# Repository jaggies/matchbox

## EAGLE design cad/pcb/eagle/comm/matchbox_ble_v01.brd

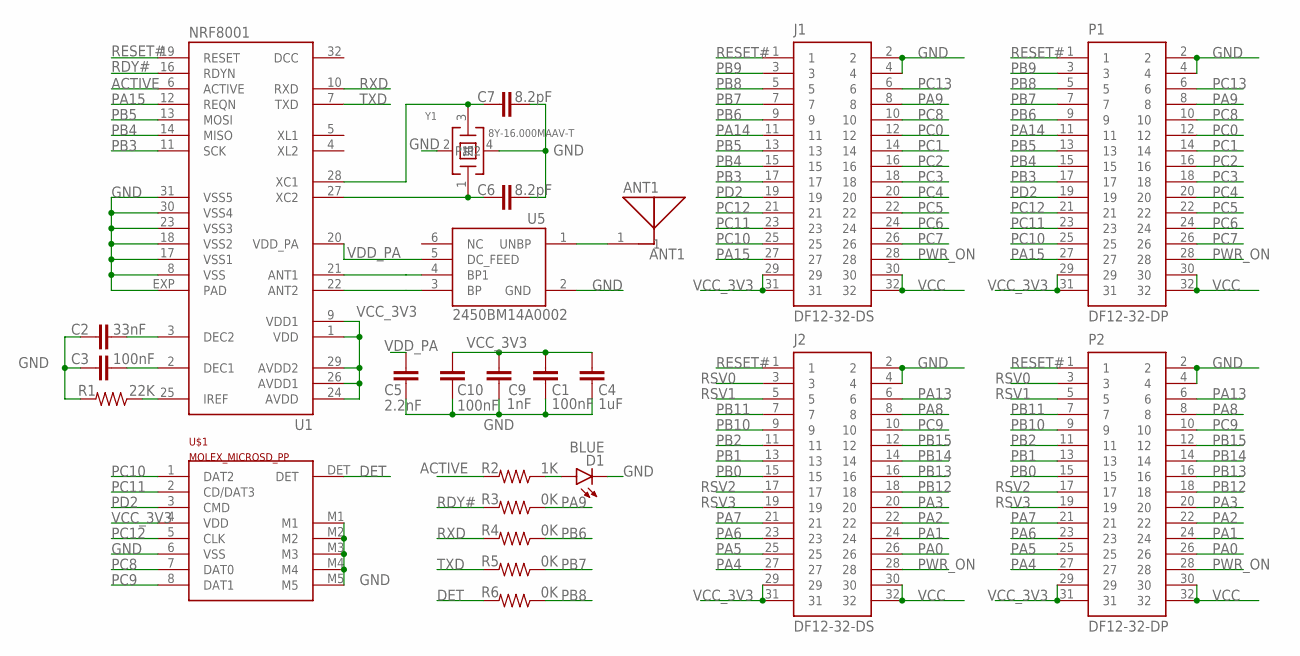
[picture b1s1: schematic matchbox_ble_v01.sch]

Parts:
ANT1: ANT1; 2450AT18A100; PARTNO AS-ITM-00132
C1, C3, C10: 100nF; 0402-CAP; MPN 1C20Z5U104M050B
C2: 33nF; 0402-CAP
C4: 1uF; 0805
C5: 2.2nF; 0402-CAP
C6, C7: 8.2pF; 0402-CAP
C9: 1nF; 0402-CAP
D1: BLUE; LED-0603
J1, J2: DF12-32-DS
P1, P2: DF12-32-DP
R1: 22K; 0402-RES
R2: 1K; 0805
R3, R4, R5, R6: 0K; 0805
U1: NRF8001; ATMEL_QFN32
U5: 2450BM14A0002
U$1: MOLEX_MICROSD_PP
Y1: 8Y-16.000MAAV-T; ABM11; PARTNO AS-ITM-00228

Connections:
ACTIVE: R2.2, U1.6 (ACTIVE)
ANT1: U1.21 (ANT1), U5.4 (BP1)
ANT2: U1.22 (ANT2), U5.3 (BP)
DET: R6.2, U$1.DET
GND: C1.2, C2.2, C3.2, C4.2, C5.2, C6.2, C7.2, C9.2, C10.2, D1.C, J1.2, J1.4, J2.2, J2.4, P1.2, P1.4, P2.2, P2.4, R1.2, U1.8 (VSS), U1.17 (VSS1), U1.18 (VSS2), U1.23 (VSS3), U1.30 (VSS4), U1.31 (VSS5), U1.EXP (PAD), U5.2 (GND), U$1.6 (VSS), U$1.M1, U$1.M2, U$1.M3, U$1.M4, U$1.M5, Y1.2, Y1.4 (P1)
unnamed: R1.1, U1.25 (IREF)
unnamed: C6.1, U1.27 (XC2), Y1.1
unnamed: C3.1, U1.2 (DEC1)
unnamed: C2.1, U1.3 (DEC2)
unnamed: ANT1.1, U5.1 (UNBP)
unnamed: C7.1, U1.28 (XC1), Y1.3 (2)
unnamed: D1.A, R2.1
PA0: J2.26, P2.26
PA1: J2.24, P2.24
PA2: J2.22, P2.22
PA3: J2.20, P2.20
PA4: J2.27, P2.27
PA5: J2.25, P2.25
PA6: J2.23, P2.23
PA7: J2.21, P2.21
PA8: J2.8, P2.8
PA9: J1.8, P1.8, R3.1
PA13: J2.6, P2.6
PA14: J1.11, P1.11
PA15: J1.27, P1.27, U1.12 (REQN)
PB0: J2.15, P2.15
PB1: J2.13, P2.13
PB2: J2.11, P2.11
PB3: J1.17, P1.17, U1.11 (SCK)
PB4: J1.15, P1.15, U1.14 (MISO)
PB5: J1.13, P1.13, U1.13 (MOSI)
PB6: J1.9, P1.9, R4.1
PB7: J1.7, P1.7, R5.1
PB8: J1.5, P1.5, R6.1
PB9: J1.3, P1.3
PB10: J2.9, P2.9
PB11: J2.7, P2.7
PB12: J2.18, P2.18
PB13: J2.16, P2.16
PB14: J2.14, P2.14
PB15: J2.12, P2.12
PC0: J1.12, P1.12
PC1: J1.14, P1.14
PC2: J1.16, P1.16
PC3: J1.18, P1.18
PC4: J1.20, P1.20
PC5: J1.22, P1.22
PC6: J1.24, P1.24
PC7: J1.26, P1.26
PC8: J1.10, P1.10, U$1.7 (DAT0)
PC9: J2.10, P2.10, U$1.8 (DAT1)
PC10: J1.25, P1.25, U$1.1 (DAT2)
PC11: J1.23, P1.23, U$1.2 (CD/DAT3)
PC12: J1.21, P1.21, U$1.5 (CLK)
PC13: J1.6, P1.6
PD2: J1.19, P1.19, U$1.3 (CMD)
PWR_ON: J1.28, J2.28, P1.28, P2.28
RDY#: R3.2, U1.16 (RDYN)
RESET#: J1.1, J2.1, P1.1, P2.1, U1.19 (RESET)
RSV0: J2.3, P2.3
RSV1: J2.5, P2.5
RSV2: J2.17, P2.17
RSV3: J2.19, P2.19
RXD: R4.2, U1.10 (RXD)
TXD: R5.2, U1.7 (TXD)
VCC: J1.30, J1.32, J2.30, J2.32, P1.30, P1.32, P2.30, P2.32
VCC_3V3: C1.1, C4.1, C9.1, C10.1, J1.29, J1.31, J2.29, J2.31, P1.29, P1.31, P2.29, P2.31, U1.1 (VDD), U1.9 (VDD1), U1.24 (AVDD), U1.26 (AVDD1), U1.29 (AVDD2), U$1.4 (VDD)
VDD_PA: C5.1, U1.20 (VDD_PA), U5.5 (DC_FEED)

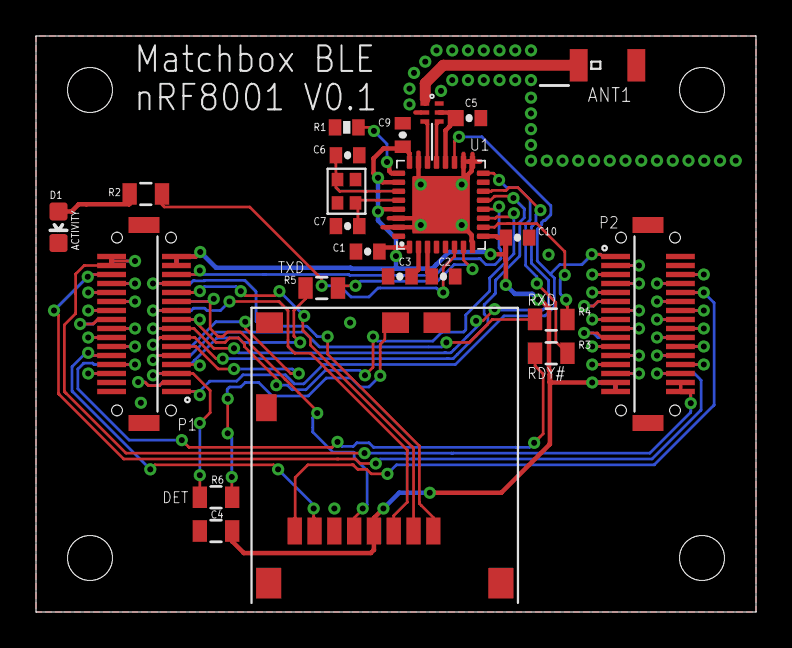
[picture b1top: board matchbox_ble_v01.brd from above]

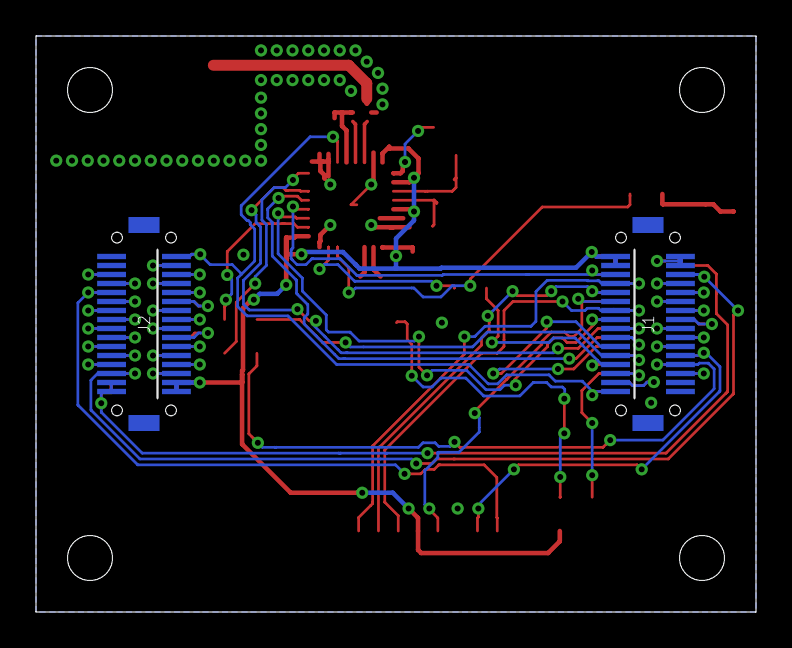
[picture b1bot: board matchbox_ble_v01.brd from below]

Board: 2 copper layers, 40.0 x 32.0 mm, 25 parts (2 on the bottom side), 68 nets.

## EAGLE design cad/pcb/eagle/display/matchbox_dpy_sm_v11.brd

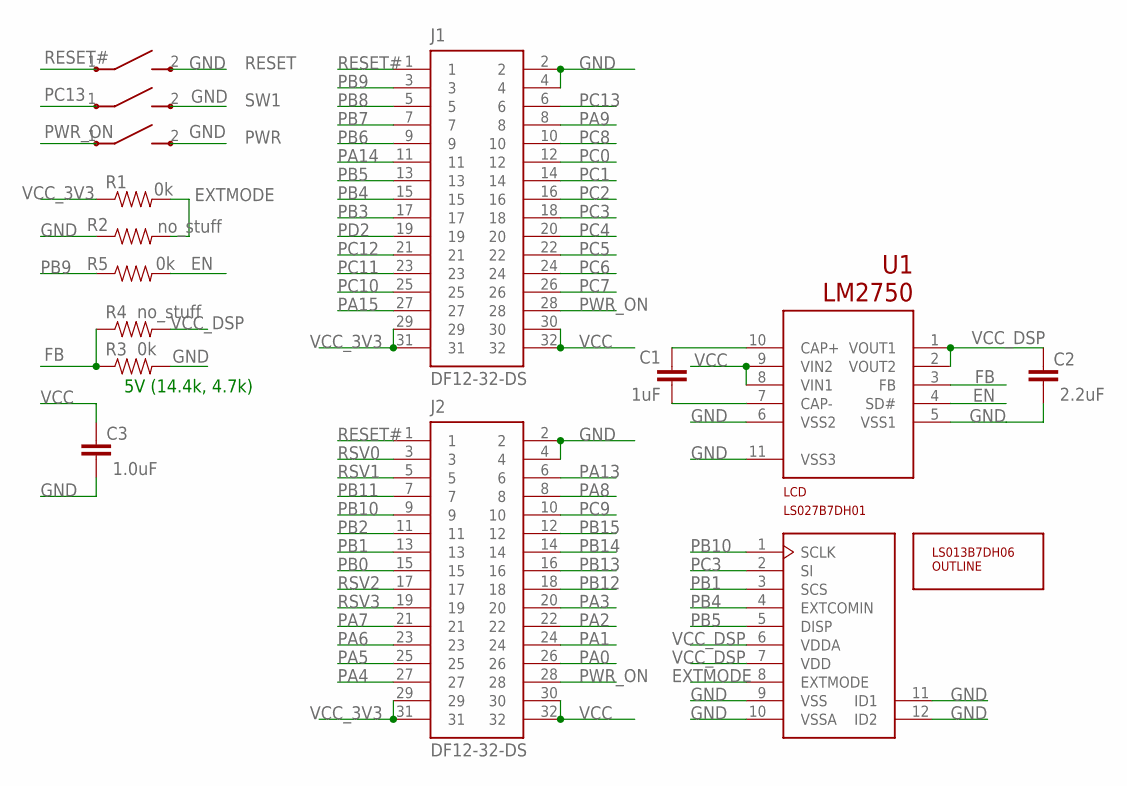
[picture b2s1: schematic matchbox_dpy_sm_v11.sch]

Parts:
C1: 1uF; 0805; MPN 106K050CS4
C2: 2.2uF; 0805; MPN 106K050CS4
C3: 1.0uF; 0805; MPN 106K050CS4
J1, J2: DF12-32-DS
LCD: LS027B7DH01; MOLEX-51441-1093
PWR: B3U-3100PM-B
R1, R3, R5: 0k; 0805
R2, R4: no_stuff; 0805
RESET: B3U-3100PM-B
SW1: B3U-3100PM-B
U1: LM2750
U$1: LS013B7DH06-OUTLINE; LS013B7DH06

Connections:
EN: R5.2, U1.4 (SD#)
EXTMODE: LCD.8 (EXTMODE), R1.2, R2.2
FB: R3.1, R4.1, U1.3 (FB)
GND: C2.2, C3.2, J1.2, J1.4, J2.2, J2.4, LCD.9 (VSS), LCD.10 (VSSA), LCD.11 (ID1), LCD.12 (ID2), PWR.2, PWR.GND, R2.1, R3.2, RESET.2, RESET.GND, SW1.2, SW1.GND, U1.5 (VSS1), U1.6 (VSS2), U1.11 (VSS3)
unnamed: C1.1, U1.10 (CAP+)
unnamed: C1.2, U1.7 (CAP-)
PA0: J2.26
PA1: J2.24
PA2: J2.22
PA3: J2.20
PA4: J2.27
PA5: J2.25
PA6: J2.23
PA7: J2.21
PA8: J2.8
PA9: J1.8
PA13: J2.6
PA14: J1.11
PA15: J1.27
PB0: J2.15
PB1: J2.13, LCD.3 (SCS)
PB2: J2.11
PB3: J1.17
PB4: J1.15, LCD.4 (EXTCOMIN)
PB5: J1.13, LCD.5 (DISP)
PB6: J1.9
PB7: J1.7
PB8: J1.5
PB9: J1.3, R5.1
PB10: J2.9, LCD.1 (SCLK)
PB11: J2.7
PB12: J2.18
PB13: J2.16
PB14: J2.14
PB15: J2.12
PC0: J1.12
PC1: J1.14
PC2: J1.16
PC3: J1.18, LCD.2 (SI)
PC4: J1.20
PC5: J1.22
PC6: J1.24
PC7: J1.26
PC8: J1.10
PC9: J2.10
PC10: J1.25
PC11: J1.23
PC12: J1.21
PC13: J1.6, SW1.1
PD2: J1.19
PWR_ON: J1.28, J2.28, PWR.1
RESET#: J1.1, J2.1, RESET.1
RSV0: J2.3
RSV1: J2.5
RSV2: J2.17
RSV3: J2.19
VCC: C3.1, J1.30, J1.32, J2.30, J2.32, U1.8 (VIN1), U1.9 (VIN2)
VCC_3V3: J1.29, J1.31, J2.29, J2.31, R1.1
VCC_DSP: C2.1, LCD.6 (VDDA), LCD.7 (VDD), R4.2, U1.1 (VOUT1), U1.2 (VOUT2)

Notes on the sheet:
5V (14.4k, 4.7k)

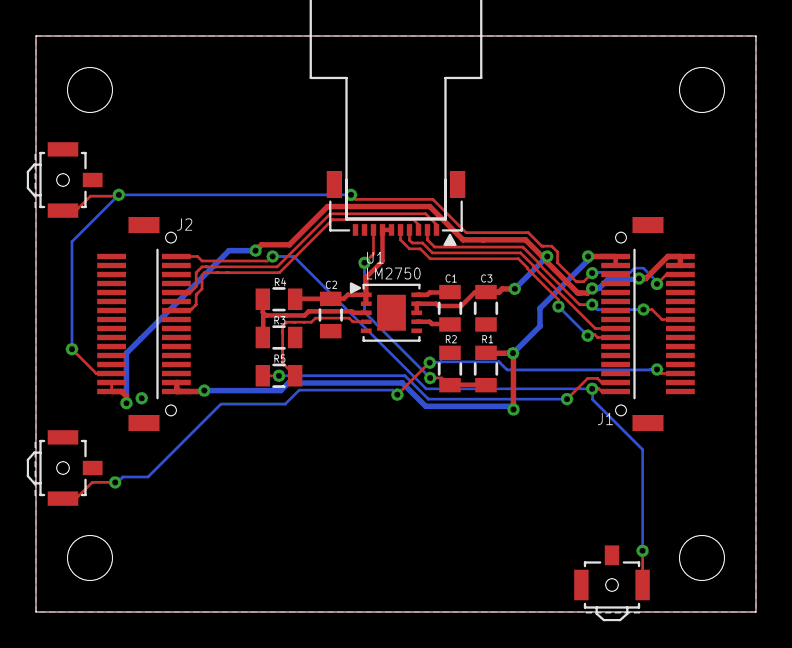
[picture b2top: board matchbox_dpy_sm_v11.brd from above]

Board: 2 copper layers, 40.0 x 32.0 mm, 16 parts (0 on the bottom side), 18 nets.

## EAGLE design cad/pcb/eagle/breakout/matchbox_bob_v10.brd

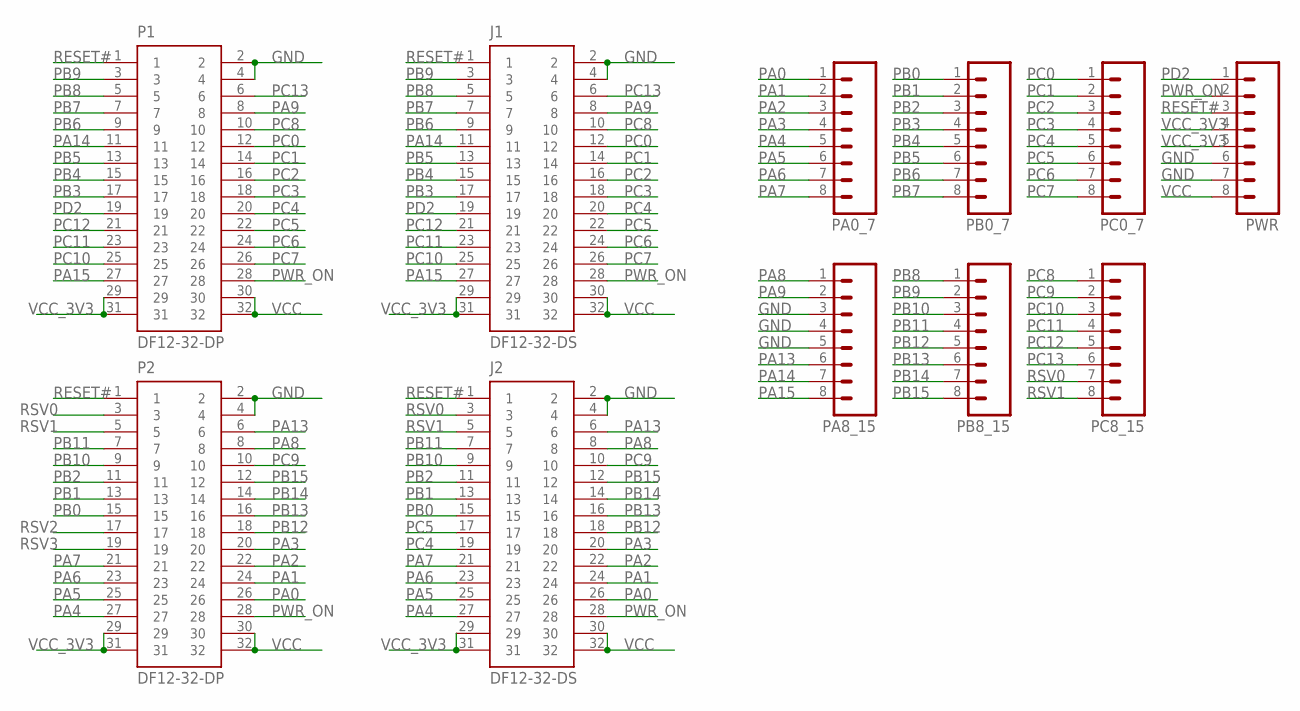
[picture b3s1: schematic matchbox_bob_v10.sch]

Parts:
J1, J2: DF12-32-DS
P1, P2: DF12-32-DP
PA0_7, PA8_15: M08FEMALE_LOCK; 1X08_FEMALE_LOCK
PB0_7, PB8_15: M08FEMALE_LOCK; 1X08_FEMALE_LOCK
PC0_7, PC8_15: M08FEMALE_LOCK; 1X08_FEMALE_LOCK
PWR: M08FEMALE_LOCK; 1X08_FEMALE_LOCK

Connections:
GND: J1.2, J1.4, J2.2, J2.4, P1.2, P1.4, P2.2, P2.4, PA8_15.3, PA8_15.4, PA8_15.5, PWR.6, PWR.7
PA0: J2.26, P2.26, PA0_7.1
PA1: J2.24, P2.24, PA0_7.2
PA2: J2.22, P2.22, PA0_7.3
PA3: J2.20, P2.20, PA0_7.4
PA4: J2.27, P2.27, PA0_7.5
PA5: J2.25, P2.25, PA0_7.6
PA6: J2.23, P2.23, PA0_7.7
PA7: J2.21, P2.21, PA0_7.8
PA8: J2.8, P2.8, PA8_15.1
PA9: J1.8, P1.8, PA8_15.2
PA13: J2.6, P2.6, PA8_15.6
PA14: J1.11, P1.11, PA8_15.7
PA15: J1.27, P1.27, PA8_15.8
PB0: J2.15, P2.15, PB0_7.1
PB1: J2.13, P2.13, PB0_7.2
PB2: J2.11, P2.11, PB0_7.3
PB3: J1.17, P1.17, PB0_7.4
PB4: J1.15, P1.15, PB0_7.5
PB5: J1.13, P1.13, PB0_7.6
PB6: J1.9, P1.9, PB0_7.7
PB7: J1.7, P1.7, PB0_7.8
PB8: J1.5, P1.5, PB8_15.1
PB9: J1.3, P1.3, PB8_15.2
PB10: J2.9, P2.9, PB8_15.3
PB11: J2.7, P2.7, PB8_15.4
PB12: J2.18, P2.18, PB8_15.5
PB13: J2.16, P2.16, PB8_15.6
PB14: J2.14, P2.14, PB8_15.7
PB15: J2.12, P2.12, PB8_15.8
PC0: J1.12, P1.12, PC0_7.1
PC1: J1.14, P1.14, PC0_7.2
PC2: J1.16, P1.16, PC0_7.3
PC3: J1.18, P1.18, PC0_7.4
PC4: J1.20, J2.19, P1.20, PC0_7.5
PC5: J1.22, J2.17, P1.22, PC0_7.6
PC6: J1.24, P1.24, PC0_7.7
PC7: J1.26, P1.26, PC0_7.8
PC8: J1.10, P1.10, PC8_15.1
PC9: J2.10, P2.10, PC8_15.2
PC10: J1.25, P1.25, PC8_15.3
PC11: J1.23, P1.23, PC8_15.4
PC12: J1.21, P1.21, PC8_15.5
PC13: J1.6, P1.6, PC8_15.6
PD2: J1.19, P1.19, PWR.1
PWR_ON: J1.28, J2.28, P1.28, P2.28, PWR.2
RESET#: J1.1, J2.1, P1.1, P2.1, PWR.3
RSV0: J2.3, P2.3, PC8_15.7
RSV1: J2.5, P2.5, PC8_15.8
RSV2: P2.17
RSV3: P2.19
VCC: J1.30, J1.32, J2.30, J2.32, P1.30, P1.32, P2.30, P2.32, PWR.8
VCC_3V3: J1.29, J1.31, J2.29, J2.31, P1.29, P1.31, P2.29, P2.31, PWR.4, PWR.5

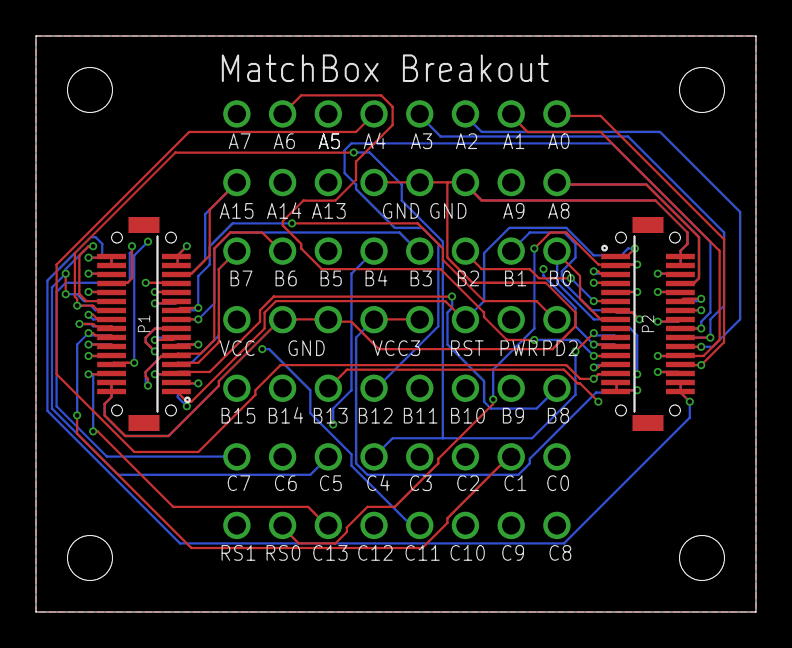
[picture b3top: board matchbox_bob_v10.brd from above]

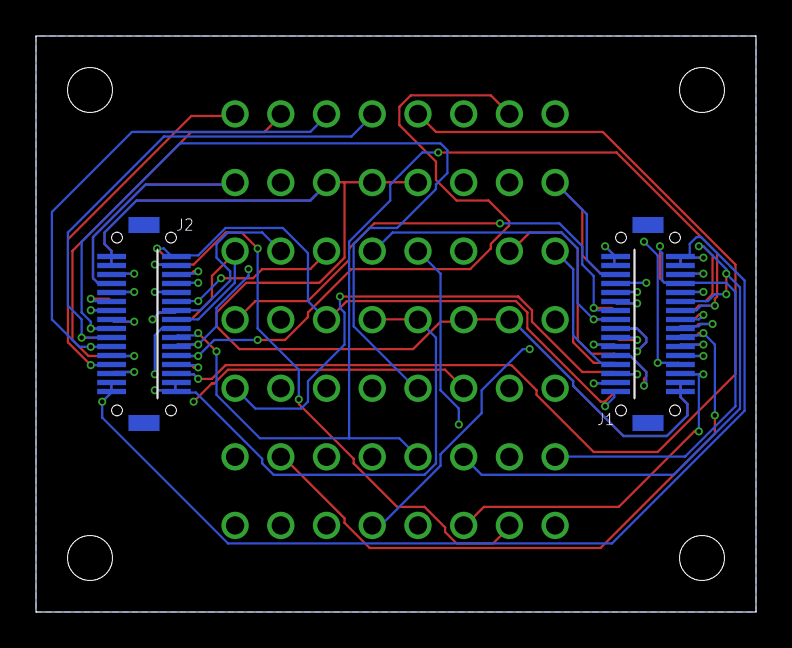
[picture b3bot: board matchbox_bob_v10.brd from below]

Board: 4 copper layers, 40.0 x 32.0 mm, 11 parts (2 on the bottom side), 51 nets.

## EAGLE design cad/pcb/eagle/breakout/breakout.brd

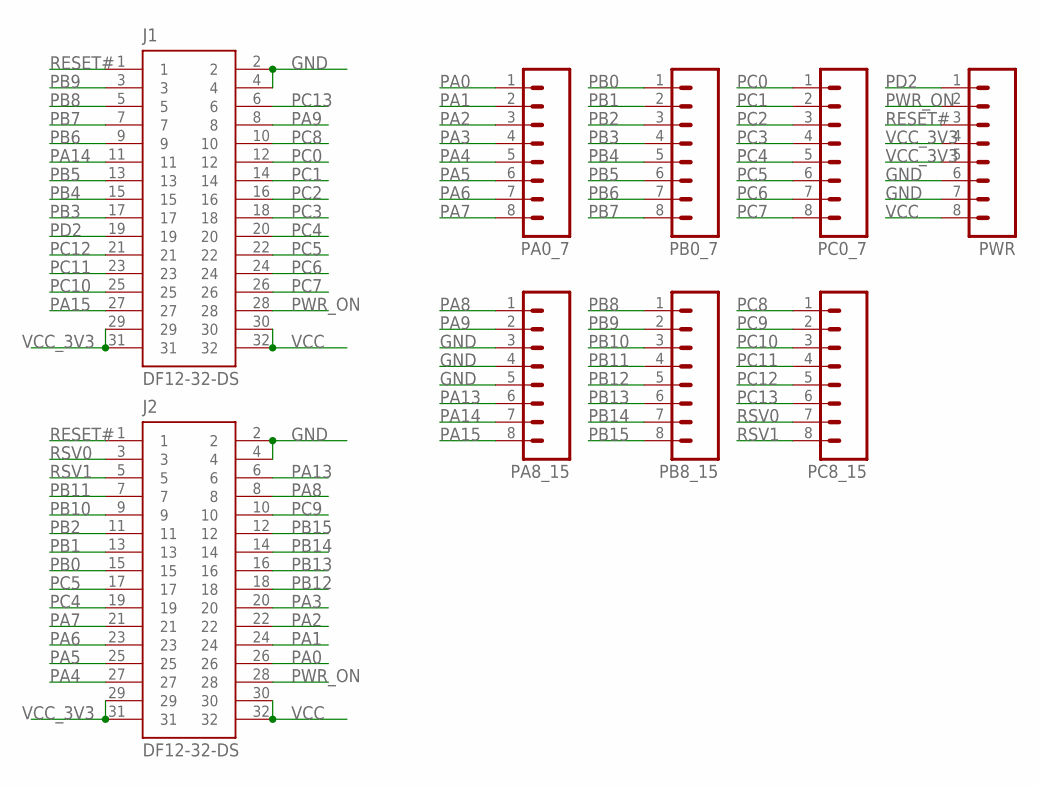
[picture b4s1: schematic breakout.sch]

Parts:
J1, J2: DF12-32-DS
PA0_7, PA8_15: M08FEMALE_LOCK; 1X08_FEMALE_LOCK
PB0_7, PB8_15: M08FEMALE_LOCK; 1X08_FEMALE_LOCK
PC0_7, PC8_15: M08FEMALE_LOCK; 1X08_FEMALE_LOCK
PWR: M08FEMALE_LOCK; 1X08_FEMALE_LOCK

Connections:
GND: J1.2, J1.4, J2.2, J2.4, PA8_15.3, PA8_15.4, PA8_15.5, PWR.6, PWR.7
PA0: J2.26, PA0_7.1
PA1: J2.24, PA0_7.2
PA2: J2.22, PA0_7.3
PA3: J2.20, PA0_7.4
PA4: J2.27, PA0_7.5
PA5: J2.25, PA0_7.6
PA6: J2.23, PA0_7.7
PA7: J2.21, PA0_7.8
PA8: J2.8, PA8_15.1
PA9: J1.8, PA8_15.2
PA13: J2.6, PA8_15.6
PA14: J1.11, PA8_15.7
PA15: J1.27, PA8_15.8
PB0: J2.15, PB0_7.1
PB1: J2.13, PB0_7.2
PB2: J2.11, PB0_7.3
PB3: J1.17, PB0_7.4
PB4: J1.15, PB0_7.5
PB5: J1.13, PB0_7.6
PB6: J1.9, PB0_7.7
PB7: J1.7, PB0_7.8
PB8: J1.5, PB8_15.1
PB9: J1.3, PB8_15.2
PB10: J2.9, PB8_15.3
PB11: J2.7, PB8_15.4
PB12: J2.18, PB8_15.5
PB13: J2.16, PB8_15.6
PB14: J2.14, PB8_15.7
PB15: J2.12, PB8_15.8
PC0: J1.12, PC0_7.1
PC1: J1.14, PC0_7.2
PC2: J1.16, PC0_7.3
PC3: J1.18, PC0_7.4
PC4: J1.20, J2.19, PC0_7.5
PC5: J1.22, J2.17, PC0_7.6
PC6: J1.24, PC0_7.7
PC7: J1.26, PC0_7.8
PC8: J1.10, PC8_15.1
PC9: J2.10, PC8_15.2
PC10: J1.25, PC8_15.3
PC11: J1.23, PC8_15.4
PC12: J1.21, PC8_15.5
PC13: J1.6, PC8_15.6
PD2: J1.19, PWR.1
PWR_ON: J1.28, J2.28, PWR.2
RESET#: J1.1, J2.1, PWR.3
RSV0: J2.3, PC8_15.7
RSV1: J2.5, PC8_15.8
VCC: J1.30, J1.32, J2.30, J2.32, PWR.8
VCC_3V3: J1.29, J1.31, J2.29, J2.31, PWR.4, PWR.5

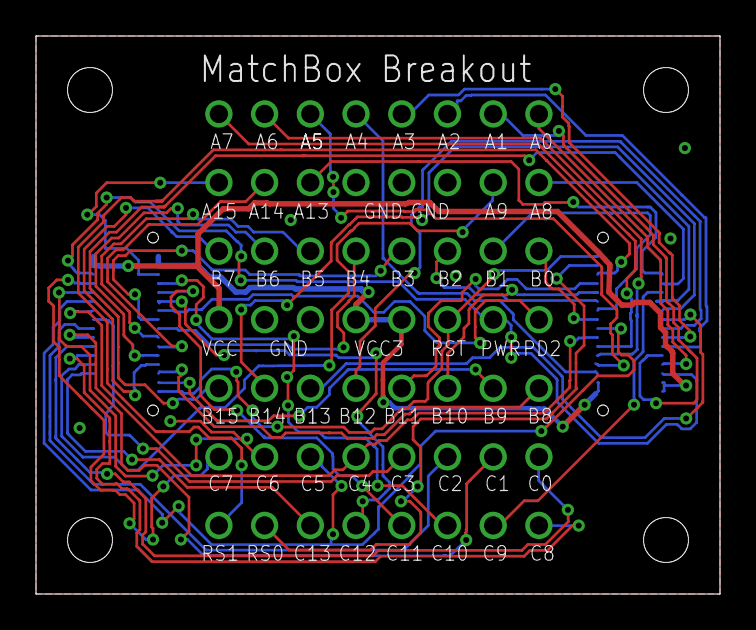
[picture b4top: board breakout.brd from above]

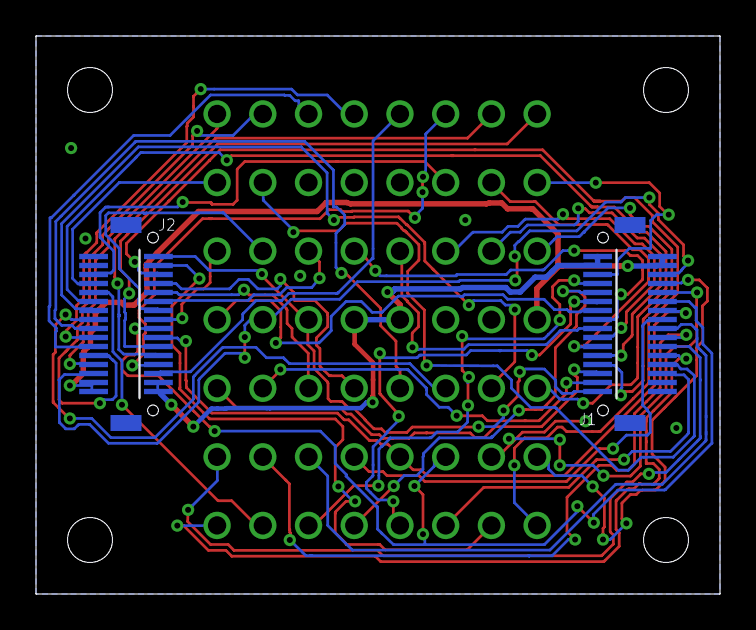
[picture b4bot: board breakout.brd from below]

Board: 2 copper layers, 38.0 x 31.0 mm, 9 parts (2 on the bottom side), 51 nets.

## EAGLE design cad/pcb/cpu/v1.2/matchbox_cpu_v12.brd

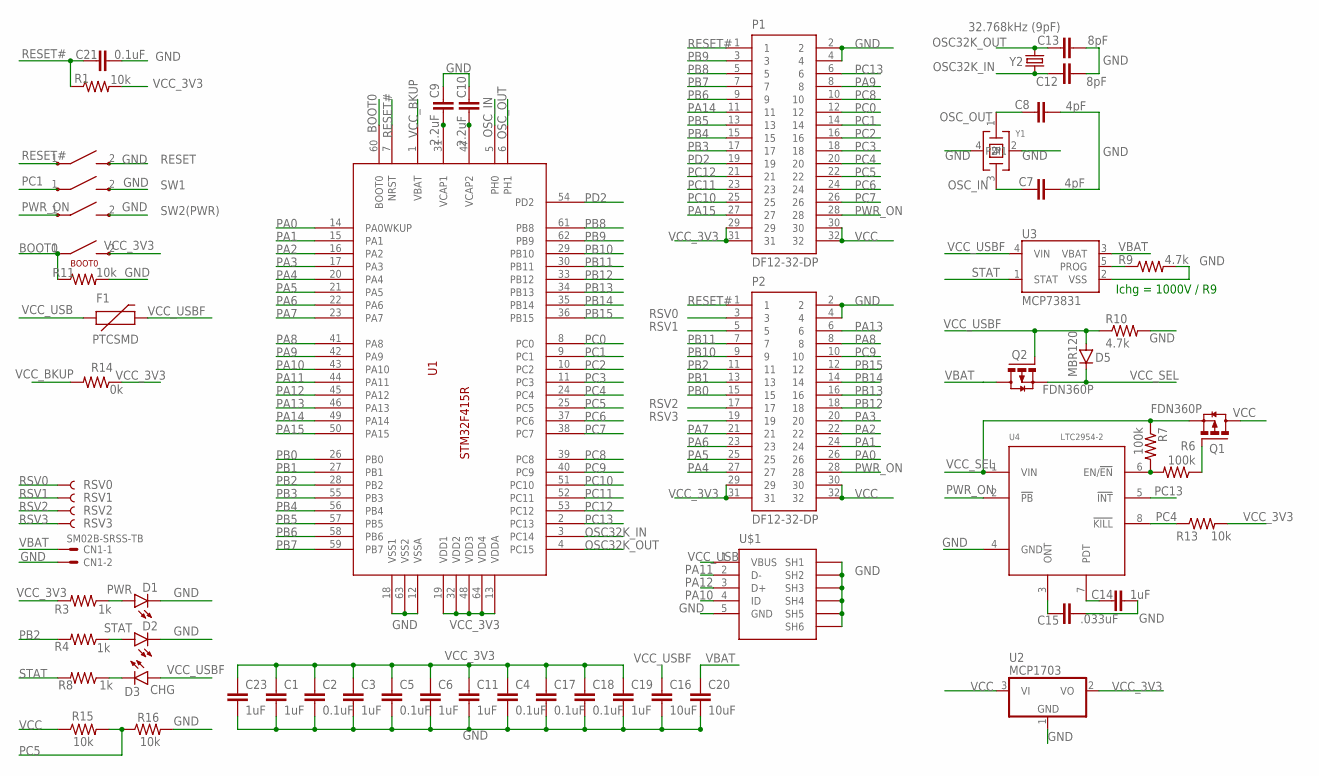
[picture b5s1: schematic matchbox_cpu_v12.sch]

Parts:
BOOT0: B3U-3100PM-B
C1, C3, C6, C11, C14, C19, C23: 1uF; 0805
C2, C4, C5, C17, C18, C21: 0.1uF; 0805
C7, C8: 4pF; 0805
C9, C10: 2.2uF; 0805
C12, C13: 8pF; 0805
C15: .033uF; 0805
C16, C20: 10uF; 0805
CN1: SM02B-SRSS-TB
D1: PWR; LED-0603
D2: STAT; LED-0603
D3: CHG; LED-0603
D5: MBR120; SOD-123
F1: PTCSMD; PTC-1206
P1, P2: DF12-32-DP
Q1, Q2: FDN360P; SUPER-SOT3
R1, R11, R13, R15, R16: 10k; 0805
R3, R4, R8: 1k; 0805
R6, R7: 100k; 0805
R9, R10: 4.7k; 0805
R14: 0k; 0805
RESET: B3U-3100PM-B
RSV0, RSV1, RSV2, RSV3: TEST-POINT3; PAD.03X.03
SW1, SW2(PWR): B3U-3100PM-B
U1: STM32F415R; LQFP64
U2: MCP1703; SOT23A
U3: MCP73831; SOT23-5
U4: LTC2954-2; SOT23-8
U$1: MICROUSB
Y1: 16MHz(9pF); ABM11
Y2: 32.768kHz (9pF); CRYSTAL-32KHZ-SMD_EPSON_MC146

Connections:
BOOT0: BOOT0.1, R11.1, U1.60 (BOOT0)
GND: BOOT0.GND, C1.2, C2.2, C3.2, C4.2, C5.2, C6.2, C7.2, C8.2, C9.1, C10.1, C11.2, C12.2, C13.2, C14.2, C15.2, C16.2, C17.2, C18.2, C19.2, C20.2, C21.2, C23.2, CN1.2, D1.C, D2.C, P1.2, P1.4, P2.2, P2.4, R9.2, R10.2, R11.2, R16.2, RESET.2, RESET.GND, SW1.2, SW1.GND, SW2(PWR).2, SW2(PWR).GND, U1.12 (VSSA), U1.18 (VSS1), U1.63 (VSS2), U2.1 (GND), U3.2 (VSS), U4.4 (GND), U$1.5 (GND), U$1.6 (SH1), U$1.7 (SH2), U$1.8 (SH3), U$1.9 (SH4), U$1.10 (SH5), U$1.11 (SH6), Y1.2, Y1.4 (P1)
unnamed: C9.2, U1.31 (VCAP1)
unnamed: C10.2, U1.47 (VCAP2)
unnamed: C15.1, U4.3 (ONT)
unnamed: C14.1, U4.7 (PDT)
unnamed: D1.A, R3.1
unnamed: D2.A, R4.1
unnamed: D3.C, R8.1
unnamed: R6.2, R7.2, U4.6 (EN/!EN!)
unnamed: Q1.1 (G), R6.1
unnamed: R9.1, U3.5 (PROG)
OSC32K_IN: C12.1, U1.3 (PC14), Y2.P$2 (1)
OSC32K_OUT: C13.1, U1.4 (PC15), Y2.P$1 (2)
OSC_IN: C7.1, U1.5 (PH0), Y1.3 (2)
OSC_OUT: C8.1, U1.6 (PH1), Y1.1
PA0: P2.26, U1.14 (PA0WKUP)
PA1: P2.24, U1.15 (PA1)
PA2: P2.22, U1.16 (PA2)
PA3: P2.20, U1.17 (PA3)
PA4: P2.27, U1.20 (PA4)
PA5: P2.25, U1.21 (PA5)
PA6: P2.23, U1.22 (PA6)
PA7: P2.21, U1.23 (PA7)
PA8: P2.8, U1.41 (PA8)
PA9: P1.8, U1.42 (PA9)
PA10: U1.43 (PA10), U$1.4 (ID)
PA11: U1.44 (PA11), U$1.2 (D-)
PA12: U1.45 (PA12), U$1.3 (D+)
PA13: P2.6, U1.46 (PA13)
PA14: P1.11, U1.49 (PA14)
PA15: P1.27, U1.50 (PA15)
PB0: P2.15, U1.26 (PB0)
PB1: P2.13, U1.27 (PB1)
PB2: P2.11, R4.2, U1.28 (PB2)
PB3: P1.17, U1.55 (PB3)
PB4: P1.15, U1.56 (PB4)
PB5: P1.13, U1.57 (PB5)
PB6: P1.9, U1.58 (PB6)
PB7: P1.7, U1.59 (PB7)
PB8: P1.5, U1.61 (PB8)
PB9: P1.3, U1.62 (PB9)
PB10: P2.9, U1.29 (PB10)
PB11: P2.7, U1.30 (PB11)
PB12: P2.18, U1.33 (PB12)
PB13: P2.16, U1.34 (PB13)
PB14: P2.14, U1.35 (PB14)
PB15: P2.12, U1.36 (PB15)
PC0: P1.12, U1.8 (PC0)
PC1: P1.14, SW1.1, U1.9 (PC1)
PC2: P1.16, U1.10 (PC2)
PC3: P1.18, U1.11 (PC3)
PC4: P1.20, R13.1, U1.24 (PC4), U4.8 (!KILL!)
PC5: P1.22, R15.2, R16.1, U1.25 (PC5)
PC6: P1.24, U1.37 (PC6)
PC7: P1.26, U1.38 (PC7)
PC8: P1.10, U1.39 (PC8)
PC9: P2.10, U1.40 (PC9)
PC10: P1.25, U1.51 (PC10)
PC11: P1.23, U1.52 (PC11)
PC12: P1.21, U1.53 (PC12)
PC13: P1.6, U1.2 (PC13), U4.5 (!INT!)
PD2: P1.19, U1.54 (PD2)
PWR_ON: P1.28, P2.28, SW2(PWR).1, U4.2 (!PB!)
RESET#: C21.1, P1.1, P2.1, R1.1, RESET.1, U1.7 (NRST)
RSV0: P2.3, RSV0.P$1
RSV1: P2.5, RSV1.P$1
RSV2: P2.17, RSV2.P$1
RSV3: P2.19, RSV3.P$1
STAT: R8.2, U3.1 (STAT)
VBAT: C20.1, CN1.1, Q2.3 (D), U3.3 (VBAT)
VCC: P1.30, P1.32, P2.30, P2.32, Q1.3 (D), R15.1, U2.3 (VI)
VCC_3V3: BOOT0.2, C1.1, C2.1, C3.1, C4.1, C5.1, C6.1, C11.1, C17.1, C18.1, C19.1, C23.1, P1.29, P1.31, P2.29, P2.31, R1.2, R3.2, R13.2, R14.1, U1.13 (VDDA), U1.19 (VDD1), U1.32 (VDD2), U1.48 (VDD3), U1.64 (VDD4), U2.2 (VO)
VCC_BKUP: R14.2, U1.1 (VBAT)
VCC_SEL: D5.C, Q1.2 (S), Q2.2 (S), R7.1, U4.1 (VIN)
VCC_USB: F1.1, U$1.1 (VBUS)
VCC_USBF: C16.1, D3.A, D5.A, F1.2, Q2.1 (G), R10.1, U3.4 (VIN)

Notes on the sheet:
Ichg = 1000V / R9

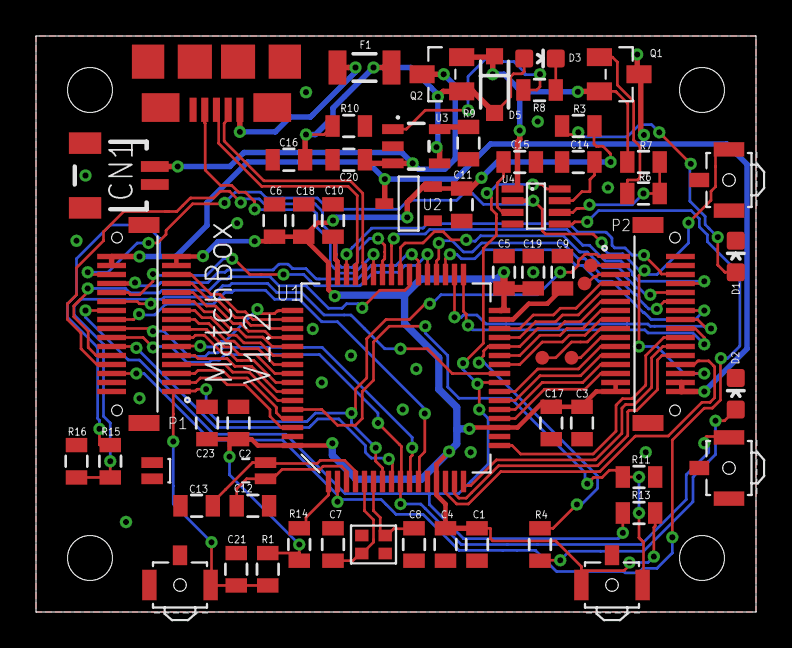
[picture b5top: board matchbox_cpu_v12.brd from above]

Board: 2 copper layers, 40.0 x 32.0 mm, 60 parts (0 on the bottom side), 77 nets.

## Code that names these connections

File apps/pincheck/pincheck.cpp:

/*
 * pincheck.cpp
 *
 *  Created on: Jul 15, 2016
 *      Author: jmiller
 */

#include <cstdio>
#include "matchbox.h"
#include "util.h"
#include "board.h"

uint64_t pups;
uint64_t drivers;
uint64_t receivers;
osThreadId defaultTaskHandle;

/**
 * Check pins for short:
 * pullUpCheck: the state of all pins during the initial pull-up. Should be all ones.
 * driver: non-zero driver bit means pin affected another pin when driven
 * receiver: list of all pins affected from drivers.
 */
void checkIoPins(uint64_t* pullUpCheck, uint64_t* driver, uint64_t* receiver) {
    static const int pins[] = {
        PA0, PA1, PA2, PA3, PA4, PA5, PA6, PA7, PA8, PA9, PA10, PA11, PA12, PA13, PA14, PA15,
        PB0, PB1, PB2, PB3, PB4, PB5, PB6, PB7, PB8, PB9, PB10, PB11, PB12, PB13, PB14, PB15,
        PC0, PC1, PC2, PC3, PC4, PC5, PC6, PC7, PC8, PC9, PC10, PC11, PC12, PC13, _PC14, _PC15 };

    for (int i = 0; i < sizeof(pins) / sizeof(pins[0]); i++) {
        pinInitInput(pins[i]); // init with pull-up
    }

    // Verify all pulled-up pins are logic '1'
    *pullUpCheck = 0ULL;
    for (int i = 0; i < Number(pins); i++) {
        *pullUpCheck |= readPin(pins[i]) ? (1ULL << pins[i]) : 0ULL;
    }

    // Pull one pin down at a time and look for other shorted pins
    *driver = *receiver = 0ULL;
    volatile int dly;
    for (int k = 0; k < Number(pins); k++) {
        if (k == PWR_KILL)
            continue; // don't kill the power!
        pinInitOutput(pins[k], 0); // pull it down
//        HAL_Delay(1); // wait for things to settle (10pF/10k = 100ns)
        dly= 100000; while (dly--) ;
        const int drv = pins[k];
        for (int i = 0; i < Number(pins); i++) {
            const int rcv = pins[i];
            if (drv != rcv && (readPin(rcv) ? 1ULL : 0ULL) != ((*pullUpCheck >> rcv) & 1ULL)) {
                // oops, unexpected pull down
                *driver |= 1ULL << drv; // driver
                *receiver |= 1ULL << rcv; // receiver
                break;
            }
        }
        pinInitInput(pins[k]); // pull it back up
    }
}

void printPinNames(uint64_t pins, uint64_t expected) {
    for (uint64_t i = 0; i < 48; i++) {
        if ((pins & (1LL << i)) != (expected << i)) {
            printf("P%c%d", "ABCD"[i>>4], i&0xf);
            if (i != 47) printf(" ");
        }
    }
}

void StartDefaultTask(void const * argument) {
    printf("HCLK: %d\n", HAL_RCC_GetHCLKFreq());
    printf("pups: %012llx (", pups);
    printPinNames(pups, 1);
    printf(")\n");

    printf("drivers: %012llx (", drivers);
    printPinNames(drivers, 0);
    printf(")\n");

    printf("receivers: %012llx (", receivers);
    printPinNames(receivers, 0);
    printf(")\n");

    // LED
    GPIO_InitTypeDef  GPIO_InitStruct = { 0 };
    GPIO_InitStruct.Pin = GPIO_PIN_2;
    GPIO_InitStruct.Mode = GPIO_MODE_OUTPUT_PP;
    GPIO_InitStruct.Pull = GPIO_NOPULL;
    GPIO_InitStruct.Speed = GPIO_SPEED_FREQ_VERY_HIGH;
    HAL_GPIO_Init(GPIOB, &GPIO_InitStruct);

    int count = 1;
    while (1) {
        HAL_GPIO_WritePin(GPIOB, GPIO_PIN_2, (count++ & 1) ? GPIO_PIN_SET : GPIO_PIN_RESET);
        HAL_Delay(500);
    }
}

void SystemClock_Config(void)
{

  RCC_OscInitTypeDef RCC_OscInitStruct;
  RCC_ClkInitTypeDef RCC_ClkInitStruct;
  __HAL_RCC_PWR_CLK_ENABLE();
  __HAL_PWR_VOLTAGESCALING_CONFIG(PWR_REGULATOR_VOLTAGE_SCALE1);

  RCC_OscInitStruct.OscillatorType = RCC_OSCILLATORTYPE_HSE;
  RCC_OscInitStruct.HSEState = RCC_HSE_ON;
  RCC_OscInitStruct.PLL.PLLState = RCC_PLL_ON;
  RCC_OscInitStruct.PLL.PLLSource = RCC_PLLSOURCE_HSE;
  RCC_OscInitStruct.PLL.PLLM = 8;
  RCC_OscInitStruct.PLL.PLLN = 72;
  RCC_OscInitStruct.PLL.PLLP = RCC_PLLP_DIV2;
  RCC_OscInitStruct.PLL.PLLQ = 3;
  HAL_RCC_OscConfig(&RCC_OscInitStruct);

  RCC_ClkInitStruct.ClockType = RCC_CLOCKTYPE_HCLK|RCC_CLOCKTYPE_SYSCLK
                              |RCC_CLOCKTYPE_PCLK1|RCC_CLOCKTYPE_PCLK2;
  RCC_ClkInitStruct.SYSCLKSource = RCC_SYSCLKSOURCE_PLLCLK;
  RCC_ClkInitStruct.AHBCLKDivider = RCC_SYSCLK_DIV1;
  RCC_ClkInitStruct.APB1CLKDivider = RCC_HCLK_DIV2;
  RCC_ClkInitStruct.APB2CLKDivider = RCC_HCLK_DIV1;
  HAL_RCC_ClockConfig(&RCC_ClkInitStruct, FLASH_LATENCY_2);
  HAL_SYSTICK_Config(HAL_RCC_GetHCLKFreq()/1000);
  HAL_SYSTICK_CLKSourceConfig(SYSTICK_CLKSOURCE_HCLK);

  /* SysTick_IRQn interrupt configuration */
  HAL_NVIC_SetPriority(SysTick_IRQn, 15, 0);
}

int main(void) {
    HAL_Init();
    SystemClock_Config();

    /* GPIO Ports Clock Enable */
    __HAL_RCC_GPIOC_CLK_ENABLE();
    __HAL_RCC_GPIOH_CLK_ENABLE();
    __HAL_RCC_GPIOA_CLK_ENABLE();
    __HAL_RCC_GPIOB_CLK_ENABLE();
    __HAL_RCC_GPIOD_CLK_ENABLE();

    checkIoPins(&pups, &drivers, &receivers);
    MatchBox* mb = new MatchBox();

    osThreadDef(defaultTask, StartDefaultTask, osPriorityNormal, 0, 2048);
    defaultTaskHandle = osThreadCreate(osThread(defaultTask), NULL);

    /* Start scheduler */
    osKernelStart();

    /* We should never get here as control is now taken by the scheduler */
    while (1)
        ;

    return 0;
}

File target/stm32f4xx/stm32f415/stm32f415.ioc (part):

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PC3.Mode=Full_Duplex_Master
PA6.Mode=Full_Duplex_Master
PH0-OSC_IN.Signal=RCC_OSC_IN
Mcu.UserName=STM32F415RGTx
PB10.Mode=Full_Duplex_Master
PC10.Signal=SDIO_D2
PC12.Signal=SDIO_CK
PA14.GPIO_Label=PWR_KILL
PA9.GPIOParameters=GPIO_Label
PA11.Mode=Device_Only
RCC.SYSCLKSource=RCC_SYSCLKSOURCE_PLLCLK
PA12.Signal=USB_OTG_FS_DP
PA4.Mode=NSS_Signal_Hard_Output
PB6.Signal=USART1_TX
PB6.Mode=Asynchronous
PC3.Signal=SPI2_MOSI
PH0-OSC_IN.Mode=HSE-External-Oscillator
RCC.HSE_VALUE=16000000
PB2.Signal=GPIO_Output
PB3.Mode=Full_Duplex_Master
PC13-ANTI_TAMP.Signal=GPIO_Input
PA15.Mode=NSS_Signal_Hard_Output
PB4.Mode=Full_Duplex_Master
PC14-OSC32_IN.Mode=LSE-External-Oscillator
PB5.Mode=Full_Duplex_Master
PC9.Mode=SD_4_bits_Wide_bus
PB7.Signal=USART1_RX
PA13.GPIOParameters=GPIO_Label
PH1-OSC_OUT.Mode=HSE-External-Oscillator
Mcu.Package=LQFP64
PA6.Signal=SPI1_MISO
PB12.Mode=NSS_Signal_Hard_Output
PA10.Signal=USB_OTG_FS_ID
PA15.Signal=SPI3_NSS
PC11.Mode=SD_4_bits_Wide_bus
PC5.Signal=SharedAnalog_PC5
PB4.Signal=SPI3_MISO
PC13-ANTI_TAMP.GPIOParameters=GPIO_Label
PA5.Mode=Full_Duplex_Master
PC15-OSC32_OUT.Mode=LSE-External-Oscillator
PB8.GPIOParameters=GPIO_Label
PA7.Mode=Full_Duplex_Master
PC13-ANTI_TAMP.GPIO_Label=SW1
PC11.Signal=SDIO_D3
PA9.GPIO_Label=NRF8K_RDYN
PC8.Signal=SDIO_D0
PC2.Signal=SPI2_MISO
PC10.Mode=SD_4_bits_Wide_bus
PC2.Mode=Full_Duplex_Master
PC14-OSC32_IN.Signal=RCC_OSC32_IN
PA13.Signal=GPIO_Input
PB8.GPIO_Label=SD_DET
PC5.GPIOParameters=GPIO_Label
PB2.GPIOParameters=GPIO_Label
PA9.Signal=GPXTI9
PC15-OSC32_OUT.Signal=RCC_OSC32_OUT
PB10.Signal=SPI2_SCK
PD2.Mode=SD_4_bits_Wide_bus
PA5.Signal=SPI1_SCK
PC12.Mode=SD_4_bits_Wide_bus
board=custom
PH1-OSC_OUT.Signal=RCC_OSC_OUT
Mcu.Name=STM32F415RGTx
PA13.GPIO_Label=SW2
PC8.Mode=SD_4_bits_Wide_bus
PB3.Signal=SPI3_SCK
PA4.Signal=SPI1_NSS
RCC.SYSCLKFreq_VALUE=168000000
PB5.Signal=SPI3_MOSI
PA12.Mode=Device_Only
PC5.GPIO_Label=VCC_MON
PA14.GPIOParameters=GPIO_Label
PA11.Signal=USB_OTG_FS_DM
PB7.Mode=Asynchronous
PA14.Signal=GPIO_Output
PB2.GPIO_Label=LED1
PB8.Signal=GPXTI8
PC9.Signal=SDIO_D1
PD2.Signal=SDIO_CMD
PB12.Signal=SPI2_NSS
PA7.Signal=SPI1_MOSI

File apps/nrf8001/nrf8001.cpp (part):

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    aci_state.aci_setup_info.setup_msgs = setup_msgs;
    aci_state.aci_setup_info.num_setup_msgs = NB_SETUP_MESSAGES;
    aci_state.aci_pins.board_name = BOARD_DEFAULT; //See boards.h for details
    aci_state.aci_pins.reqn_pin = PA15; // SS pin for nRF8001
    aci_state.aci_pins.rdyn_pin = PA9; // Interrupt pin from nRF8001
    aci_state.aci_pins.mosi_pin = PB5; // SPI data -> nRF8001
    aci_state.aci_pins.miso_pin = PB4; // SPI data <- nRF8001
    aci_state.aci_pins.sck_pin = PB3; // SPI clk
    aci_state.aci_pins.spi_clock_divider = 0; // TODO: Should be ~2MHz
    aci_state.aci_pins.reset_pin = UNUSED_PIN;
    aci_state.aci_pins.active_pin = UNUSED_PIN;
    aci_state.aci_pins.optional_chip_sel_pin = UNUSED_PIN;
    aci_state.aci_pins.interface_is_interrupt = false; // use interrupt handler for RDY#, else poll
    aci_state.aci_pins.interrupt_number = 1;

    // Reset nRF8001 with hardware line, if available.
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
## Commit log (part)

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2019-06-15 Add doc directory and ignore Debug.
2019-06-15 Reduce heap size (UNTESTED)
2019-06-15 Fix debugging printf
    error() only logs if debugging is enabled
    since it's pointless to log to a dead serial port.
2019-06-15 Minor optimization in LCD::clear().
2019-06-19 Remove rgb from calls in favor of setColor() method for speed.
2019-06-20 Expose font bitmap width/height
2020-05-25 Fix build on Linux
2020-05-25 Initial battery design
2020-05-25 Slightly deeper battery holder
2020-05-25 Battery holder with basic cuts (no extrusions)
2020-05-25 Added button cutouts
2020-05-25 Add cuts, but don't remove material yet
2020-05-25 More button cutout work
2020-05-25 Add retainer extrusion
2020-05-25 Switch to 1.5mm wall thickness
2020-05-25 More wall tweaks
2020-05-25 More battery compartment tweaks
2020-05-25 More final
2020-05-25 More tweaks
2020-05-25 Minor corrections after print verification
2020-05-25 More corrective tweaks
2020-05-25 Slight variation on tolerance relaxation
2020-05-25 Slight variation on tolerance relaxation.. part 2
2020-05-25 Add LCD cutouts to battery compartment
2020-05-25 Add buttons to new battery compartment
2020-05-25 Add battery wire cutout
2020-05-25 More tweaks to wire cutout
2020-05-25 Add display case
2020-05-25 Display case tweaks
2020-05-25 Minor display tweaks
2020-05-25 Switch to 1.9mm wall for display
2020-05-25 1.9mm wall cleanup
2020-05-25 Switch to 1.75mm wall thickness
2020-05-25 Switch to 1.75mm wall thickness... continued
2020-05-25 Display 1.5mm wall tweaks
2020-05-25 More 1.5mm wall display tweaks
2020-05-25 Shrink display retaining pins to 1.22mm
2020-05-25 More 1.75mm wall tweaks
2020-05-25 First corner piece
2020-05-25 Corner tinkering
2020-05-25 Initial corner with peg design
2020-05-25 Tweaked corner with pegs
2020-05-25 Add screw corner pieces with hole
2020-05-25 Tweak screw corners
2020-05-25 New corner design tweaks
2020-05-25 Relax tolerance with smaller 2.44mm pin
2020-05-25 Rename newbattery -> new_battery
2020-05-25 No battery case tweaks.
2020-05-25 Lower battery case with button correction
2020-05-25 Rename standard corner to peg-corner
2020-05-25 First jimduino version.
2020-05-25 Add LIPO charging circuit.
2020-05-25 Add more intelligent power switching and improve schematic layout.
2020-06-06 Release candidate 0
2020-06-06 Release Candidate 1
2020-06-06 Release Candidate 2
2020-06-06 New USB connector
2020-06-06 Final v1.0 cpu
2020-06-06 Use new side switches
2020-06-06 Change capacitance values. Final build?
2020-06-06 Add CPU version 1.2
2020-06-06 Add breakout board
2020-06-06 Tweak board
2020-06-06 Better routing
2020-06-06 Matchbox breakout board v1.0 (40x32mm)
2020-06-06 Tweaks to BOB v1.0
2020-06-06 Add matchbox BOB v1.1
2020-06-06 Initial matchbox display schematic & board
2020-06-06 Add display board v1.0
2020-06-06 Add display board v1.1
2020-06-06 BT tweaks
2020-06-06 More progress on v01 BLE
2020-06-06 Add VDDA supply (WIP)
2020-06-06 Final BLE board
2020-06-08 Define system clock to be 16MHz. Fix GCC warnings.
2020-06-08 Update flash script to use python3
2020-06-08 Use simpler raster operations to avoid using multiply per pixel.
2020-06-08 Add span() and special case clear performance for all black/all white
2020-06-08 Reuse stored already-stored pixels to fill the rest in clear().
2020-06-10 Minor LCD performance improvements
    - add span() primitive
    - move small routines to header for inlining
2020-06-10 Expose system clock configuration at runtime (Untested)
2020-06-11 Import STM32Cube_FW_F4_V1.25.0
2020-06-11 Get code roughly compiling.
    Import new ffconf.h
    Import new std32f4xx_hal_conf.h
    Fix renamed structures for SD files.
    Update USB_LL to use uint32_t size transfers (may fix old hang bug)
    Document hal_msp.c overloads
    LCDtest works, but is slow.
2020-06-11 Fix warnings about changed types.
2020-06-11 Add bridge directory and start porting sd code (WIP)
2020-06-11 All code now compiles and links.
    Threadtest and LCDtest both run, but the latter is really slow
2020-06-12 Create bridge device handlers for SD and USB (WIP)
    Hello.cpp works, but hangs after sending text.
2020-06-12 Clean up usbserial write operations.
2020-06-12 Change usb descriptor to "Generic"
2020-06-12 Fix sd_diskio variants.
2020-06-12 Enable wide bus operation in sdio_test (untested)
2020-06-13 Add linecoding support in attempt to get Linux to see something other than /dev/ttyACM*
2020-06-14 Fix USBSerial read (woot!)
    Formerly, the protocol wasn't implemented correctly, which caused
    an on-device hang when the USB FIFO was full.
    stdio::read() should now be able to read from the fifo (untested)
2020-06-14 Fix type-o in ReadBlocks
2020-06-14 Fix slow drawing on lcdtest by lowering SPI frequency
    Unknown why this only happens on STM32 V1.25. Presumably
    another IRQ is firing frequently and blocking this one.
    Investigation for another day...
2020-06-14 Set configuration closer to original matchbox config.
2020-06-15 Checkpoint:
    write appears to work if 1s delay is introduced between
    writes.
2020-06-16 Use LED to show callbacks instead of printf, which results in bad things
2020-06-16 sdio_dma_test works!!!
    The code required the addition of a loop to ensure non-overlapping
    DMA transfers to the SD cad. In short, follow the same code in
    sd_diskio_dma_rtos_bspv1.c which loops on BSP_SD_GetCardState()
    to check the transfer state after each operation.
2020-06-16 Improve sdio_dma_test to be more predictable.
    Read/write is expected to complete before returning, so do that.
2020-06-16 Update sdio_test with same completion logic as sdio_dma_test.
    Still has issues writing, especially on startup. Guessing these
    are related to the 'f415 errata about hardware flow control bugs.
2020-06-16 Fix BSP SDIO test case (DMA only)
2020-06-16 Got fatfs working again. Turns out the BSP completion routines weren't being called. May fix other tests as well (TODO)
2020-06-16 Clean up fatfs test printout
2020-06-16 Wait for SD card on startup for fatfs test.
2020-06-16 Bump CPU to 168MHz.
    Benchmarks on 16GB card:
    1.1MB write
    1.05MB read
2020-06-17 File cleanup.
2020-06-17 Add IDLE handler hook for apps to use to achieve lower power.
    Have LCD code yield the process while waiting for swapbuffers to occur.
    This cut the power in half for threadtest (from 72.9mA to 36.1mA)
2020-06-20 Use pre/post sleep hooks to further reduce power to 22.9mA
    Test conditions: matchbox CPU only (no daughter cards).
2020-06-20 Some further power improvements
    16MHz: 8.9mA
    24MHz: 9.1mA
    168MHz: 22.7mA
    Test condition: CPU only (no daughter cards)
2020-06-20 Get RTC running (WIP)
    Runs on internal oscillator, but way too fast.
2020-06-20 Handle newlines in font rendering
    Fix font rendering to know about max character width/height
2020-06-20 RTC app now prints to LCD instead of USB
2020-06-20 Improve putString/putChar routines to track raster position between calls.
    Should also improve performance. Still more to do.
2020-06-20 Use larger font in rtc test app.
    Also eliminate sleep waiting for USB since we don't use it anymore.
2020-06-20 USB delay require to prevent hang (fixme!)
2020-06-22 Hide PC14 and PC15 since they're used for the LSE oscillator
2020-06-22 Successfully initialized LSE (I think). At least no errros.
2020-06-22 Add freertos dependency to bletest
2020-06-22 LSE clock is probably working now, but needs a higher divisor than expected. The instructions in code want to be 1/1000th of the current value (32 instead of 32768)
2020-06-22 Save some power using larger divisor from datasheet.
    Also, ensure rtc app and main library use the same divisor sources.
2020-06-22 Add roboto-bold-32 font and use it in clock app
2020-06-22 Print in differnt fonts and ensure LCD command buffer gets updated in case pixels overflow into command area
2020-06-22 Run at super slow CPU speed to make performance improvements obvious.
2020-06-24 Only wait for vertical retrace if in double-buffer mode.
    Also, force-updates lcd SPI buffer in double buffer mode in
    case it gets overwritten by drawing commands. TODO: clip so this
    can't happen.
2020-06-24 More RTC refactoring
2020-06-24 Disable RTC backup domain after setting calendar.
2020-06-24 Attempt to fix time loss after every reset.
    Before this change, every reset caused the clock to loose nearly a
    second after reset. After this change, it still looses time unless
    we transition from the matchbox entrypoint to the bootloader
    to normal state. Likely memory state corryption.
    Will probably work fine with battery backup, but needs investigation.
2020-06-24 Use large font for date as well in RTC demo.
2020-06-24 Finally solve RTC losing 1 second per reset problem.
    The power-on reset flag was persisting since nobody clears it.
    So now we do...
2020-06-24 Always return 24h format so fatfs time is correct.
2020-06-24 Remove duplicate and global hrtc value.
2020-06-25 Add method to render to the front buffer where we don't really need double buffering.
2020-06-25 Add chip documentation
2020-06-26 Get 1 BLE channel working reliably showing sin wave.
2020-07-01 Add CPU v2 (WIP)
2020-07-01 More CPU v20 changes
2020-07-02 Routed CPU v2.0. Needs cleanup.
2020-07-02 Cleaned up decoupling caps and layout to maximize copper area.
2020-07-02 Add "tag-connect" JTAG connector to schematic
2020-07-02 Basic CPU v2.0 with connections and some cleanup work.
2020-07-03 Remove unnecessary RESET# pin pullup
2020-07-03 Add STM32CubeF4 as a submodule
2020-07-03 Add STM experimental repo as submodule
2020-07-03 Clean up CPUv2 component labels
2020-07-04 Ensure proper LCD startup by clearing line buffers to scan content.
2020-07-04 Hide EagleCad lock files.
2020-07-04 Remove links from lib/hal directory
    Jamfiles are now distributed in STM32CubeF4 directory.
2020-07-04 Add Vref bypass caps.
2020-07-04 Update footprints with KiCAD parts
2020-07-05 Improved bypass strategy: vias with local caps.
2020-07-05 Fix all labels and 3D rendering
2020-07-05 Add 3d crysta modesl and use correct Hirost connector on CPUv2
2020-07-05 Bypass cap improvements for STM32 part
2020-07-05 Minor ground plane improvements
2020-07-05 Fix all DRC errors with undefined courtyards
2020-07-06 P3 and P2 got swapped. Swap them back.
2020-07-06 Add D1 3d model back in.
2020-07-06 Set gerber parameters
2020-07-06 Updated RESET and BOOT0 since Kicad insists on changing the name every time I update the PCB
2020-07-07 Add place-holder SOIC-8 QPSI components
2020-07-07 Fully routed QSPI devices
2020-07-07 Add decoupling capacitors for QSPI parts
2020-07-07 More ground tweaking after attempting to add JTAG connector. Not enough room!
2020-07-08 Finishing touches
    - Move switches to +6mm from mounting holes
    - Use text instead of references for silkscreen
    - Add debug test points
    - Add test points for serial port 1
    - Clean up all silk screen labels
2020-07-08 Ignore H7 stuff in master until branch is merged.
2020-07-08 Fix misaligned fill polygons. They now match the cut outline.
2020-07-08 Ignore temporary gerber files
2020-07-08 Tune ground plane around SD card
2020-07-08 Minor cleanup before sending out for fab - Replace STM32H743VI with STM32H753VI which is currently easier to get - Fix mislabeled CN1 issue (now called BATT1) - Fix mislabeled wires on STM part for 1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
2020-07-09 Fix footprint issues on P1, P2 and P3 as well as CPU
    After uploading, I noticed some traces would hang off the respective
    pads, which will make soldering error-prone on these parts. Too late
    for this batch, maybe next.
2020-07-21 Checkpoint multi-target work
2020-07-21 Add digikey part numbers to schematic and create script to parse them into bom
2020-07-21 Move device-specific targets into target directories
2020-07-21 Refactor build to target separate directories for different devices.
    Compiles for target=STM32F4XX by default (untested)
    Compiles the H7 HAL driver but barfs on stm32f4xx-specific bridge code
    which will need to be partitioned.
2020-07-22 Add LCSC part numbers and take snapshot of working gerber settings
2020-07-24 Add script to generate header from cubemx pin csv file.
2020-07-24 Rename lib/compat to lib/arduino
2020-07-24 Use pin mapping from STMCubeMX tool
2020-07-24 Remove more device dependencies
    Also fixes race condition in build caused by multiple occurrences of port.c
2020-07-25 Fix H7 build (WIP)
2020-07-25 More device-specific build stuff for H7 vs F4
2020-07-25 Add configuration for stm32f415 and generate code

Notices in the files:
parts and their libraries:
GeekAmmo: Licensing:Creative Commons ShareAlike 4.0 International - https://creativecommons.org/licenses/by-sa/4.0
